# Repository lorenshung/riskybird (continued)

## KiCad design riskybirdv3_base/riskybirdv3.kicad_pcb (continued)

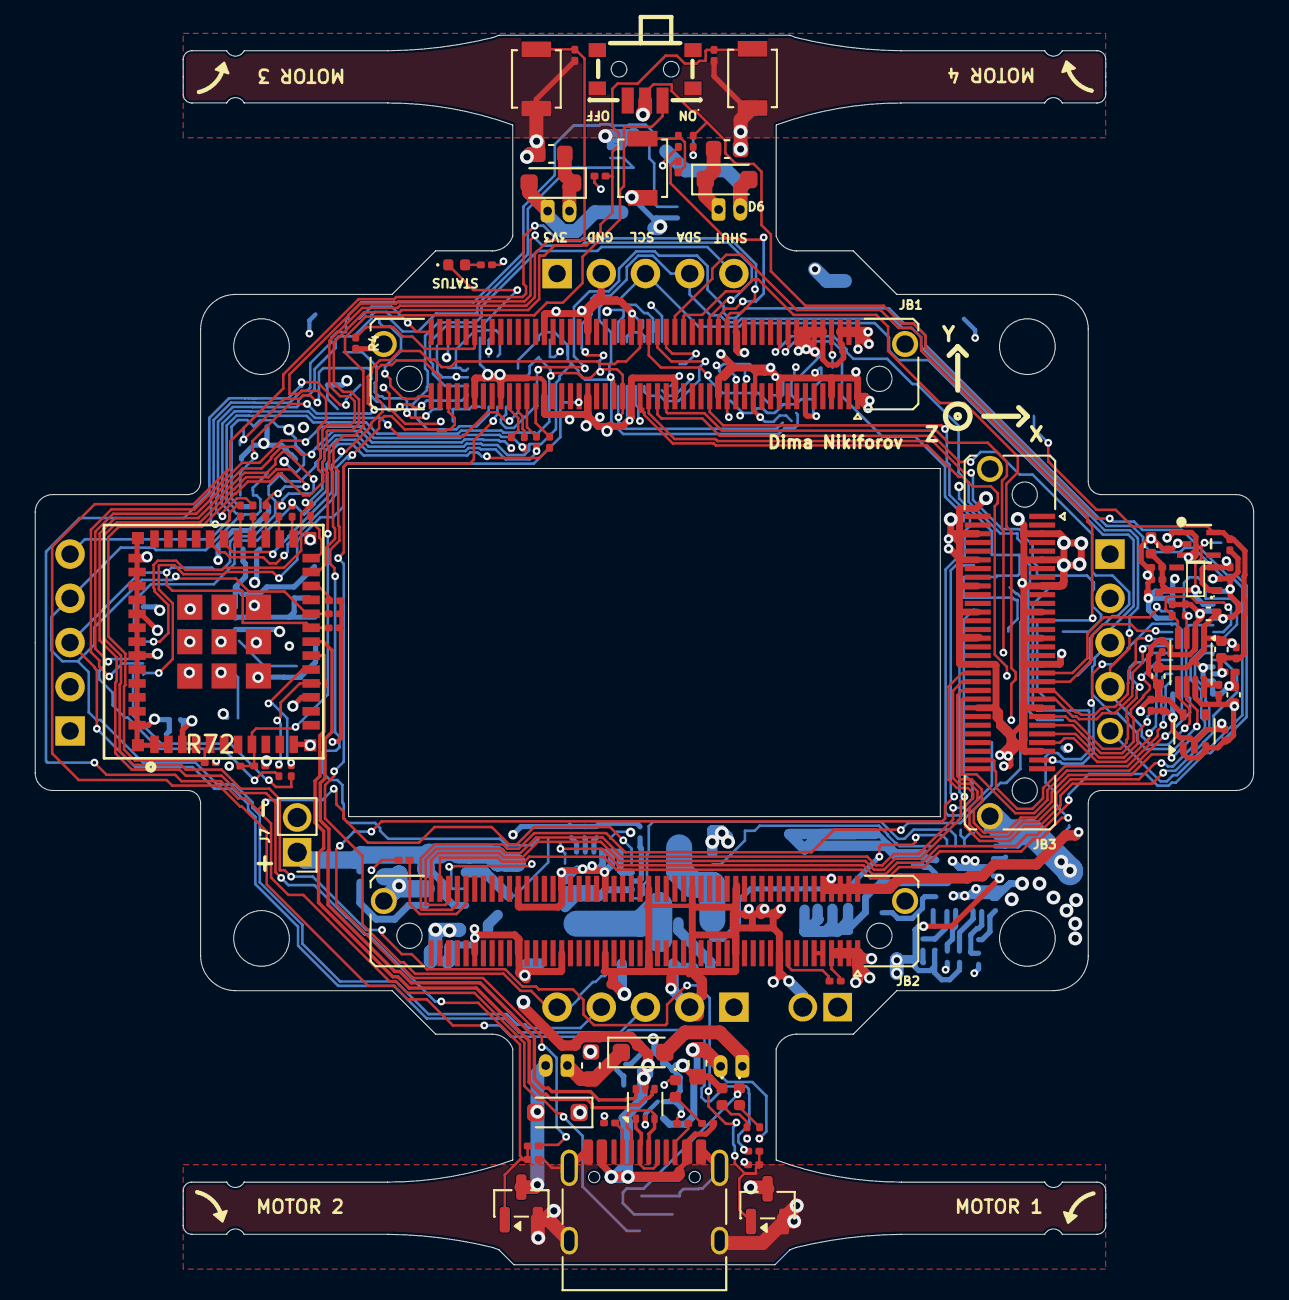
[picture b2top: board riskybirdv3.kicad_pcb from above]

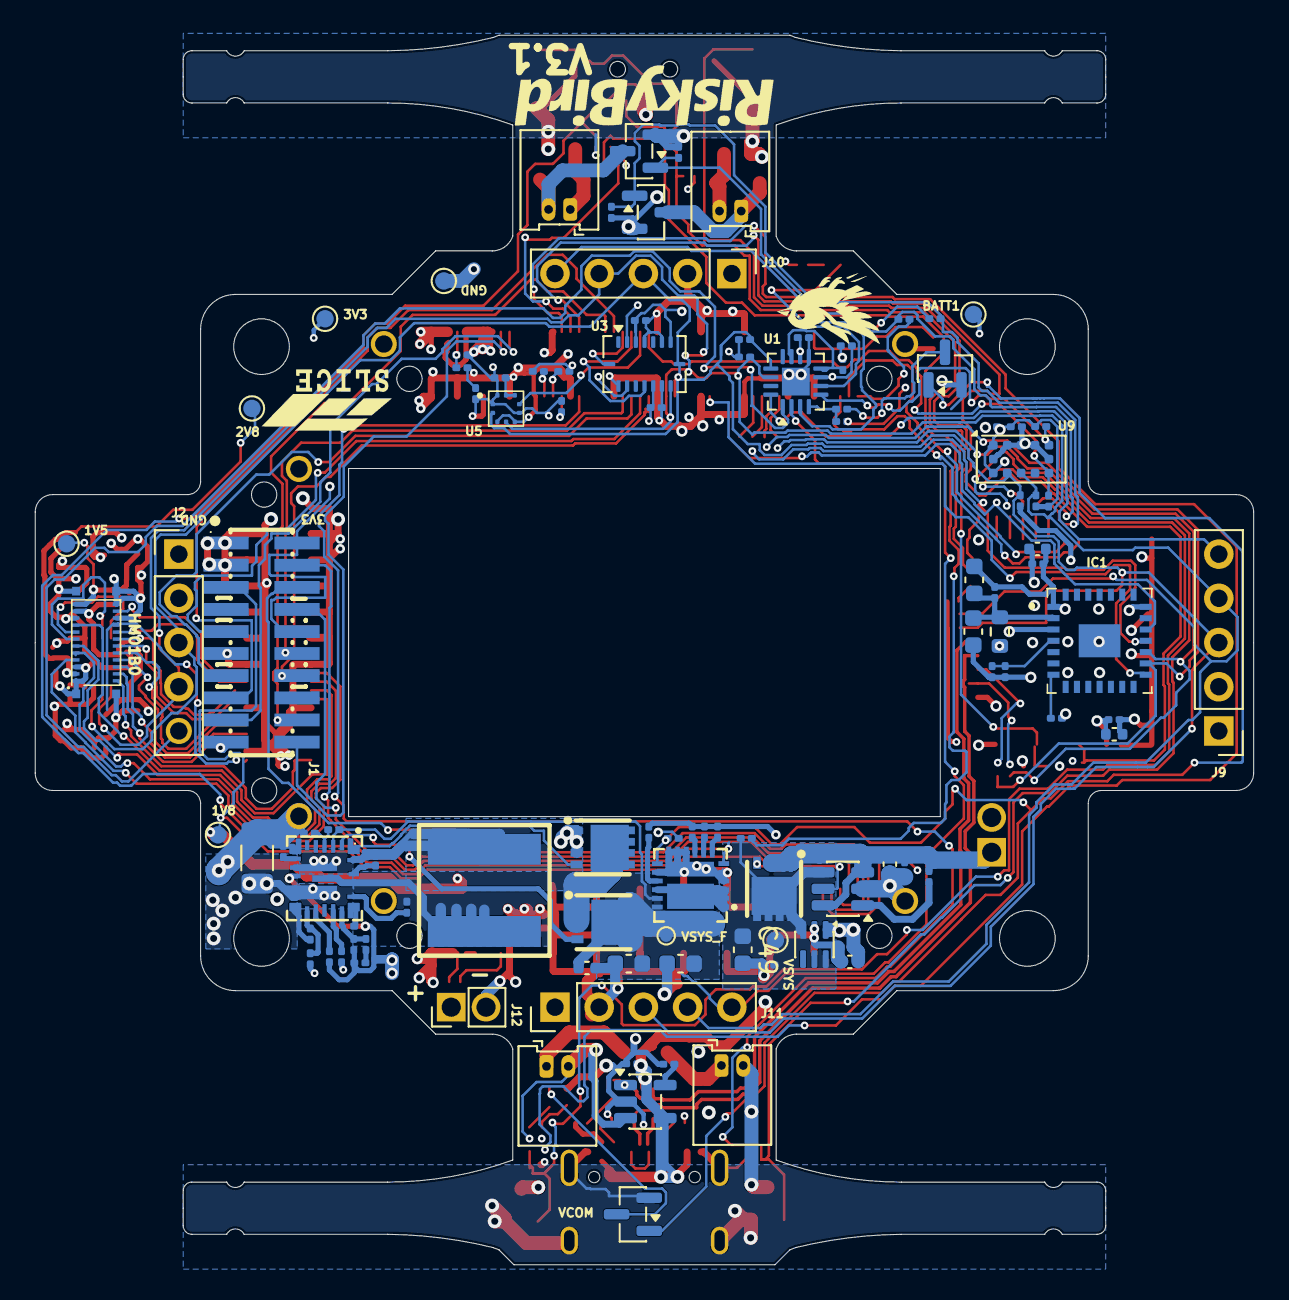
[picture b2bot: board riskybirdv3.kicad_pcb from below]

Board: 4 copper layers, 70.0 x 70.6 mm, 199 parts (108 on the bottom side), 138 nets.

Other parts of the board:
G1: LOGO

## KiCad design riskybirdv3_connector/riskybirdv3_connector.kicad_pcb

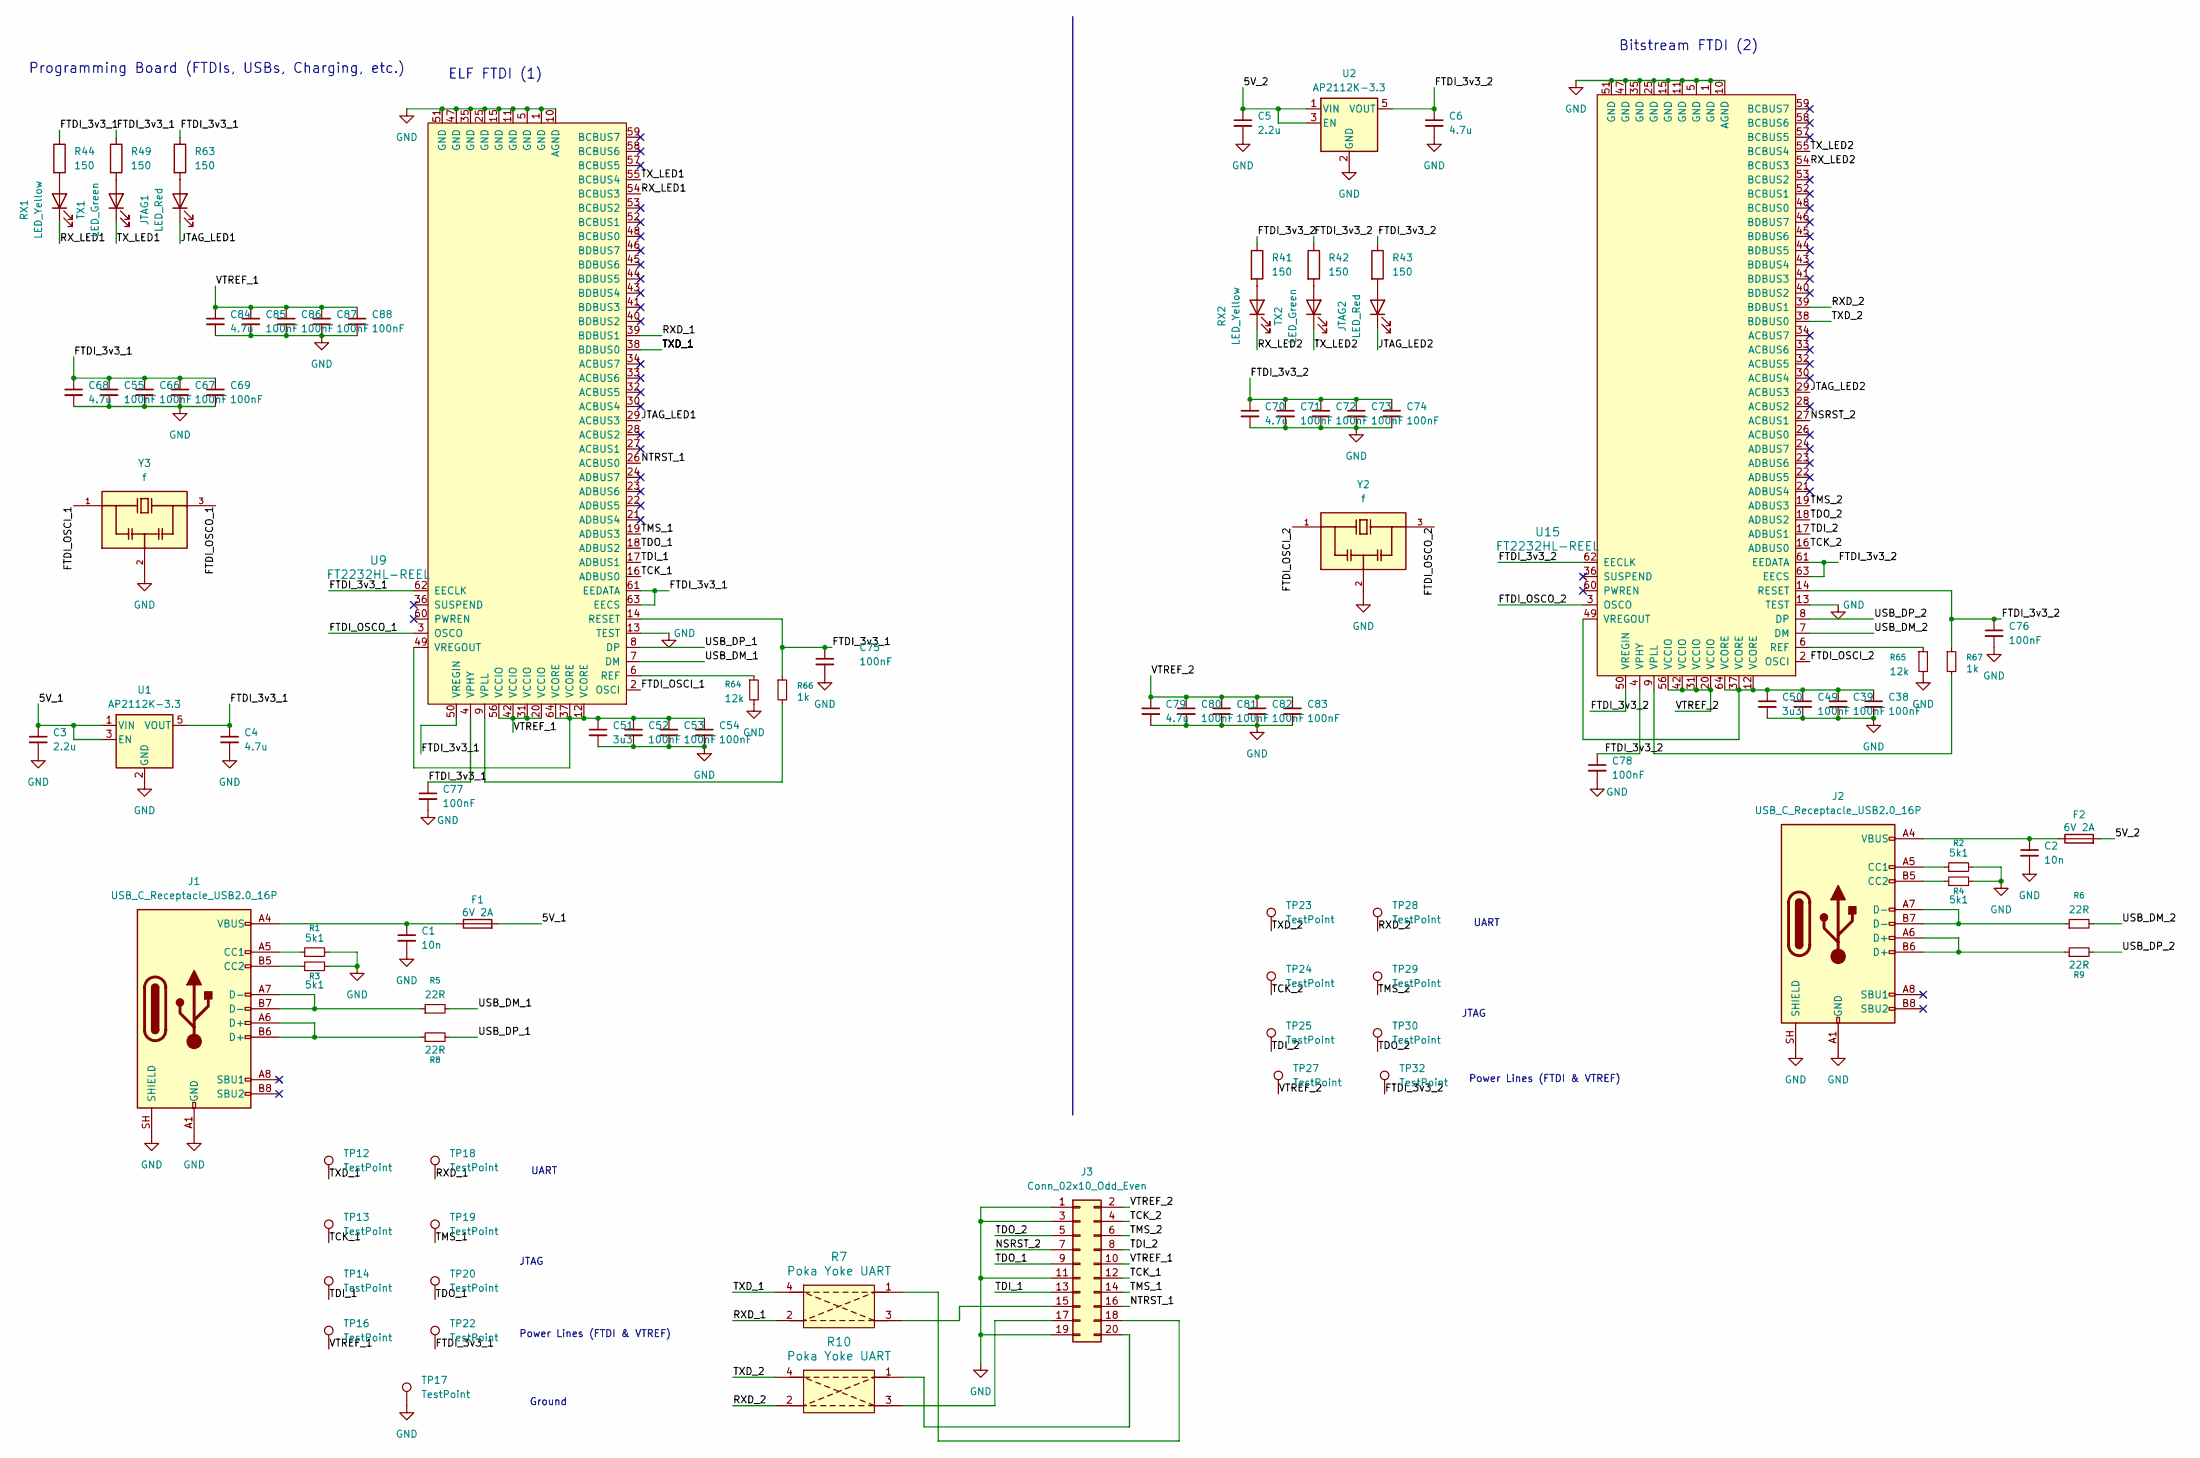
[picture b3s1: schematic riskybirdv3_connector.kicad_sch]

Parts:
C1, C2: 10n; C_0201_0603Metric; MPN 0201B103K250NT; LCSC Part C285010
C3, C5: 2.2u; C_0201_0603Metric; MPN GRM033R61A225ME47D; LCSC Part C319184
C4, C6, C68, C70, C79, C84: 4.7u; C_0201_0603Metric; MPN GRM035R60J475ME15D; LCSC Part C335103
C38, C39, C49, C52, C53, C54, C55, C66, C67, C69, C71, C72, C73, C74, C75, C76, C77, C78, C80, C81, C82, C83, C85, C86, C87, C88: 100nF; C_0201_0603Metric; MPN GRM033R61E104KE14D; LCSC Part C76939
C50, C51: 3u3; C_0201_0603Metric; MPN CL03A305MQ37RNZ; LCSC Part C514591
F1, F2: 6V 2A; Fuse_1210_3225Metric; MPN BSMD1210-200-6V; LCSC Part C914221
J1, J2: USB_C_Receptacle_USB2.0_16P; USB_C_Receptacle_GCT_USB4105-xx-A_16P_TopMnt_Horizontal; MPN USB4105-GF-A-060; LCSC Part C3025063
J3: Conn_02x10_Odd_Even; CONN-SMD_FTSH-110-01-L-DV-K-TR; MPN FTSH-110-01-L-DV-K-TR; LCSC Part C20728453
JTAG1, JTAG2: LED_Red; LED_0402_1005Metric; MPN NCD0402R1; LCSC Part C130719
R1, R2, R3, R4: 5k1; R_0201_0603Metric; MPN 0201WMF5101TEE; LCSC Part C270344
R5, R6, R8, R9: 22R; R_0201_0603Metric; MPN RC0201FR-0722RL; LCSC Part C155743
R7, R10: Poka Yoke UART; poka_yoke_uart_SMD
R41, R42, R43, R44, R49, R63: 150; R_0201_0603Metric; MPN RC0201FR-07150RL; LCSC Part C295773
R64, R65: 12k; R_0201_0603Metric; MPN 0201WMF1202TEE; LCSC Part C270363
R66, R67: 1k; R_0201_0603Metric; MPN 0201WMF1001TEE; LCSC Part C270365
RX1, RX2: LED_Yellow; LED_0402_1005Metric; MPN SZYY0402Y; LCSC Part C434450
TP12, TP13, TP14, TP16, TP17, TP18, TP19, TP20, TP22, TP23, TP24, TP25, TP27, TP28, TP29, TP30, TP32: TestPoint; TestPoint_Pad_D1.0mm
TX1, TX2: LED_Green; LED_0402_1005Metric; MPN SZYY0402YG; LCSC Part C434449
U1, U2: AP2112K-3.3; SOT-23-5; MPN AP2112K-3.3TRG1; LCSC Part C23380830
U9, U15: FT2232HL-REEL; LQFP-64_10x10mm_P0.5mm; MPN FT2232HL-REEL; LCSC Part C27882
Y2, Y3: f; OSC_CSTNE12M0G550000R0; MPN CSTNE12M0G550000R0; LCSC Part C341520

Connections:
/5V_1: C3.1, F1.2, U1.1 (VIN), U1.3 (EN)
/5V_2: C5.1, F2.2, U2.1 (VIN), U2.3 (EN)
/FTDI_3v3_1: C4.1, C55.1, C66.1, C67.1, C68.1, C69.1, C75.1, C77.1, R44.1, R49.1, R63.1, R66.1, TP22.1 (1_1), U1.5 (VOUT), U9.4 (VPHY), U9.14 (RESET), U9.50 (VREGIN), U9.61 (EEDATA), U9.62 (EECLK), U9.63 (EECS)
/FTDI_3v3_2: C6.1, C70.1, C71.1, C72.1, C73.1, C74.1, C76.1, C78.1, R41.1, R42.1, R43.1, R67.1, TP32.1 (1_1), U2.5 (VOUT), U15.4 (VPHY), U15.14 (RESET), U15.50 (VREGIN), U15.61 (EEDATA), U15.62 (EECLK), U15.63 (EECS)
/FTDI_OSCI_1: U9.2 (OSCI), Y3.1
/FTDI_OSCI_2: U15.2 (OSCI), Y2.1
/FTDI_OSCO_1: U9.3 (OSCO), Y3.3
/FTDI_OSCO_2: U15.3 (OSCO), Y2.3
/JTAG_LED1: JTAG1.1 (K), U9.29 (ACBUS3)
/JTAG_LED2: JTAG2.1 (K), U15.29 (ACBUS3)
/NSRST_2: J3.7, U15.27 (ACBUS1)
/NTRST_1: J3.16, U9.26 (ACBUS0)
/RXD_1: R7.2, TP18.1 (1_1), U9.39 (BDBUS1)
/RXD_2: R10.2, TP28.1 (1_1), U15.39 (BDBUS1)
/RX_LED1: RX1.1 (K), U9.54 (BCBUS3)
/RX_LED2: RX2.1 (K), U15.54 (BCBUS3)
/TCK_1: J3.12, TP13.1 (1_1), U9.16 (ADBUS0)
/TCK_2: J3.4, TP24.1 (1_1), U15.16 (ADBUS0)
/TDI_1: J3.13, TP14.1 (1_1), U9.17 (ADBUS1)
/TDI_2: J3.8, TP25.1 (1_1), U15.17 (ADBUS1)
/TDO_1: J3.9, TP20.1 (1_1), U9.18 (ADBUS2)
/TDO_2: J3.5, TP30.1 (1_1), U15.18 (ADBUS2)
/TMS_1: J3.14, TP19.1 (1_1), U9.19 (ADBUS3)
/TMS_2: J3.6, TP29.1 (1_1), U15.19 (ADBUS3)
/TXD_1: R7.4, TP12.1 (1_1), U9.38 (BDBUS0)
/TXD_2: R10.4, TP23.1 (1_1), U15.38 (BDBUS0)
/TX_LED1: TX1.1 (K), U9.55 (BCBUS4)
/TX_LED2: TX2.1 (K), U15.55 (BCBUS4)
/USB_DM_1: R5.2, U9.7 (DM)
/USB_DM_2: R6.2, U15.7 (DM)
/USB_DP_1: R8.2, U9.8 (DP)
/USB_DP_2: R9.2, U15.8 (DP)
/VTREF_1: C84.1, C85.1, C86.1, C87.1, C88.1, J3.10, TP16.1 (1_1), U9.20 (VCCIO), U9.31 (VCCIO), U9.42 (VCCIO), U9.56 (VCCIO)
/VTREF_2: C79.1, C80.1, C81.1, C82.1, C83.1, J3.2, TP27.1 (1_1), U15.20 (VCCIO), U15.31 (VCCIO), U15.42 (VCCIO), U15.56 (VCCIO)
GND: C1.2, C2.2, C3.2, C4.2, C5.2, C6.2, C38.2, C39.2, C49.2, C50.2, C51.2, C52.2, C53.2, C54.2, C55.2, C66.2, C67.2, C68.2, C69.2, C70.2, C71.2, C72.2, C73.2, C74.2, C75.2, C76.2, C77.2, C78.2, C79.2, C80.2, C81.2, C82.2, C83.2, C84.2, C85.2, C86.2, C87.2, C88.2, J1.A1 (GND), J1.A12 (GND), J1.B1 (GND), J1.B12 (GND), J1.SH (SHIELD), J2.A1 (GND), J2.A12 (GND), J2.B1 (GND), J2.B12 (GND), J2.SH (SHIELD), J3.1, J3.3, J3.11, J3.19, R1.2, R2.2, R3.2, R4.2, R64.2, R65.2, TP17.1 (1_1), U1.2 (GND), U2.2 (GND), U9.1 (GND), U9.5 (GND), U9.10 (AGND), U9.11 (GND), U9.13 (TEST), U9.15 (GND), U9.25 (GND), U9.35 (GND), U9.47 (GND), U9.51 (GND), U15.1 (GND), U15.5 (GND), U15.10 (AGND), U15.11 (GND), U15.13 (TEST), U15.15 (GND), U15.25 (GND), U15.35 (GND), U15.47 (GND), U15.51 (GND), Y2.2, Y3.2
unnamed: C1.1, F1.1, J1.A4 (VBUS), J1.A9 (VBUS), J1.B4 (VBUS), J1.B9 (VBUS)
unnamed: C2.1, F2.1, J2.A4 (VBUS), J2.A9 (VBUS), J2.B4 (VBUS), J2.B9 (VBUS)
unnamed: R41.2, RX2.2 (A)
unnamed: R42.2, TX2.2 (A)
unnamed: JTAG2.2 (A), R43.2
unnamed: R44.2, RX1.2 (A)
unnamed: R49.2, TX1.2 (A)
unnamed: JTAG1.2 (A), R63.2
unnamed: J1.A5 (CC1), R1.1
unnamed: J1.B5 (CC2), R3.1
unnamed: J1.A6 (D+), J1.B6 (D+), R8.1
unnamed: J1.A7 (D-), J1.B7 (D-), R5.1
unnamed: J2.A5 (CC1), R2.1
unnamed: J2.B5 (CC2), R4.1
unnamed: J2.A6 (D+), J2.B6 (D+), R9.1
unnamed: J2.A7 (D-), J2.B7 (D-), R6.1
unnamed: J3.15, R7.3
unnamed: J3.17, R10.3
unnamed: J3.18, R7.1
unnamed: J3.20, R10.1
unnamed: R64.1, U9.6 (REF)
unnamed: R66.2, U9.9 (VPLL)
unnamed: C51.1, C52.1, C53.1, C54.1, U9.12 (VCORE), U9.37 (VCORE), U9.49 (VREGOUT), U9.64 (VCORE)
unnamed: R65.1, U15.6 (REF)
unnamed: R67.2, U15.9 (VPLL)
unnamed: C38.1, C39.1, C49.1, C50.1, U15.12 (VCORE), U15.37 (VCORE), U15.49 (VREGOUT), U15.64 (VCORE)

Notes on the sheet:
Programming Board (FTDIs, USBs, Charging, etc.)
JTAG
UART
ELF FTDI (1)
Power Lines (FTDI & VTREF)
Bitstream FTDI (2)
Ground

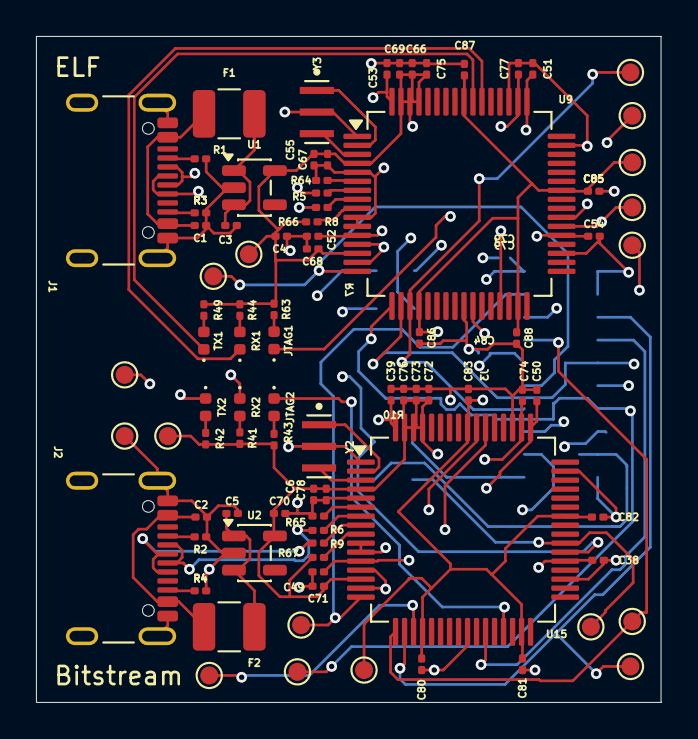
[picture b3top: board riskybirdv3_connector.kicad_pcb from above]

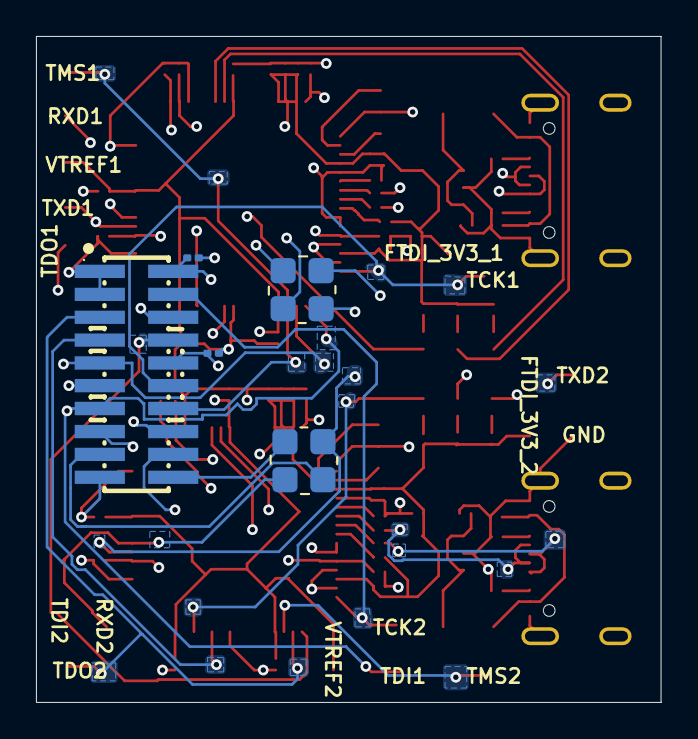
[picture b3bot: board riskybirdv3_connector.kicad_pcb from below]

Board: 4 copper layers, 34.7 x 37.0 mm, 92 parts (5 on the bottom side), 61 nets.

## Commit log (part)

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2025-12-10 ADD: V2 Files
2025-12-10 UPDATE: V2 Files
2025-12-10 FIX: broke something
2026-01-22 Remove temporary/backup files from tracking and add .gitignore
2026-01-22 first revision of riskybirdv2 sensor board
2026-01-22 rename sensorboard project directory
2026-02-06 initial esp board commit
2026-04-22 draft for H-frame riskybird
2026-05-29 update camera part
2026-06-03 Project was moved to the native VCS repository (Versioned Storage) in your Altium Server. Your local project (local repository) now needs to be switched to point to this new remote repository. Please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
2026-06-12 update documentation
2026-06-24 docs: add ECO-001 3v3 supply & power front-end redesign proposal
    Buck-boost (LTC3119) replacing the non-functional TPS54331 buck for a
    flat 3.3V rail across the full 1S discharge; uprated power mux (TPS2117,
    4A) and an SW3-gated high-side P-FET load switch replacing the 0.3A
    slide switch in the main path. Single +3V3 rail; drops U12 LDO + U13
    output mux. For review before schematic edits.
2026-06-26 docs: add schematic hierarchy / sheet-split partition plan
    Component->sheet mapping for all 179 parts across 7 functional sheets
    (Power, SoM, Sensors, Camera, ESP32, USB/Debug, Motors&IO) + the
    cross-sheet signals to convert to global labels. Behavior-preserving
    split to do before ECO-001 lands in the Power sheet; verified by
    netlist node-membership equivalence.
